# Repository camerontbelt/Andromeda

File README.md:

## An easy to use discrete 4 bit DAC
Andromeda is an easy to use, discrete, four bit DAC. It has been designed for higher voltages in mind, utilizing a 741 op amp you can attain ~+/-23 volts. It also contains an on board potentiometer for input offset voltage adjustments.

### What you will need
* External plus and minus power supply
* Four switches or a MCU for input @ 5V

### Uses
* Digitally adjustable breadboard power supply
* Fine tuned millivolt or microvolt supply
* The board itself can also be used as a summing amplifier if input resistors are adjusted.

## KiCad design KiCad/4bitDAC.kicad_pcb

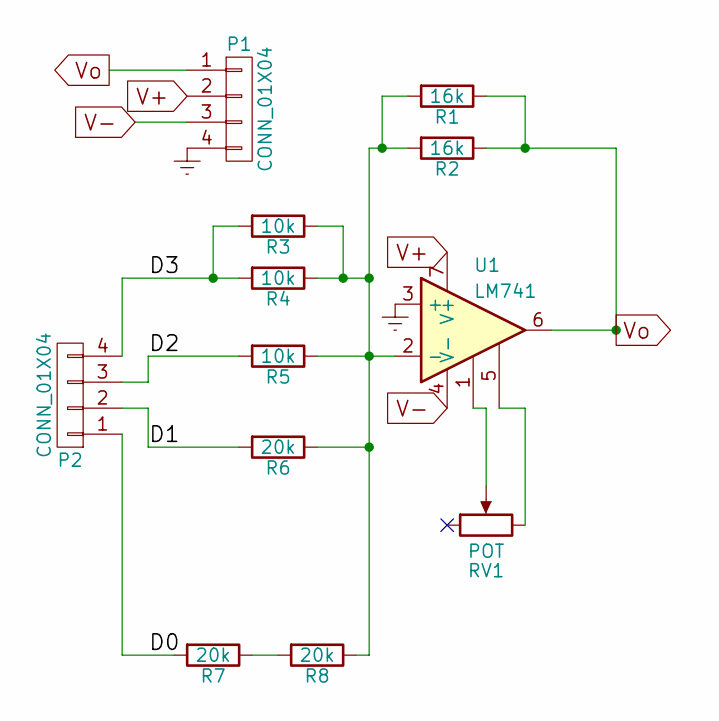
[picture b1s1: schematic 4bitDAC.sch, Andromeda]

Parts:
P1, P2: CONN_01X04; Pin_Header_Straight_1x04_Pitch2.54mm
R1, R2: 16k; Resistor_SMD+THTuniversal_0805to1206_RM10_HandSoldering
R3, R4, R5: 10k; Resistor_SMD+THTuniversal_0805to1206_RM10_HandSoldering
R6, R7, R8: 20k; Resistor_SMD+THTuniversal_0805to1206_RM10_HandSoldering
RV1: POT; Potentiometer_Trimmer_ACP_CA9h2.5_Vertical_Px2.5mm_Py5.0mm
U1: LM741; DIP-8_W7.62mm_LongPads

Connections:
/D0: P2.1, R7.2
/D1: P2.2, R6.2
/D2: P2.3, R5.2
/D3: P2.4, R3.2, R4.2
Earth: P1.4, U1.3 (+)
unnamed: R1.2, R2.2, R3.1, R4.1, R5.1, R6.1, R8.1, U1.2 (-)
unnamed: R7.1, R8.2
unnamed: RV1.2, U1.1
unnamed: RV1.3, U1.5
V+: P1.2, U1.7 (V+)
V-: P1.3, U1.4 (V-)
Vo: P1.1, R1.1, R2.1, U1.6

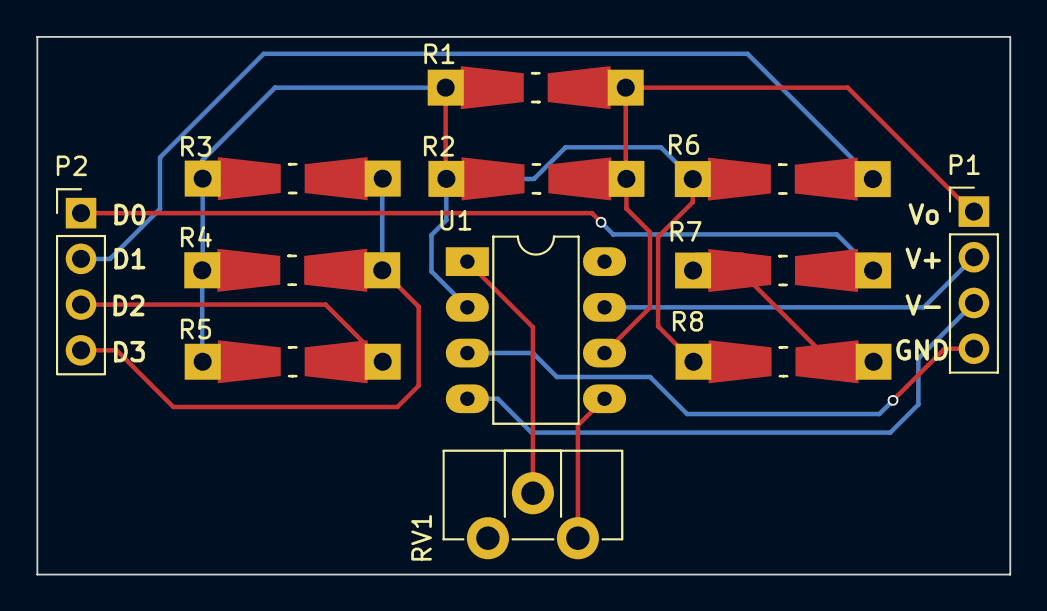
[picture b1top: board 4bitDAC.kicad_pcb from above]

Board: 2 copper layers, 54.1 x 29.9 mm, 13 parts (1 on the bottom side), 12 nets.

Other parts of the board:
logo: logo

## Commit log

2017-12-18 Added template folders, blank bom, and blank README.md file.
2017-12-18 In process of editing PCB.
2017-12-19 Finalized PCB, added gerbers and drill files, added schematic pdf.
2017-12-19 Added board images to images folder.
2017-12-19 Edited README.md
2017-12-22 Filled in BoM data.
2017-12-22 Finalized digikey part number column.
